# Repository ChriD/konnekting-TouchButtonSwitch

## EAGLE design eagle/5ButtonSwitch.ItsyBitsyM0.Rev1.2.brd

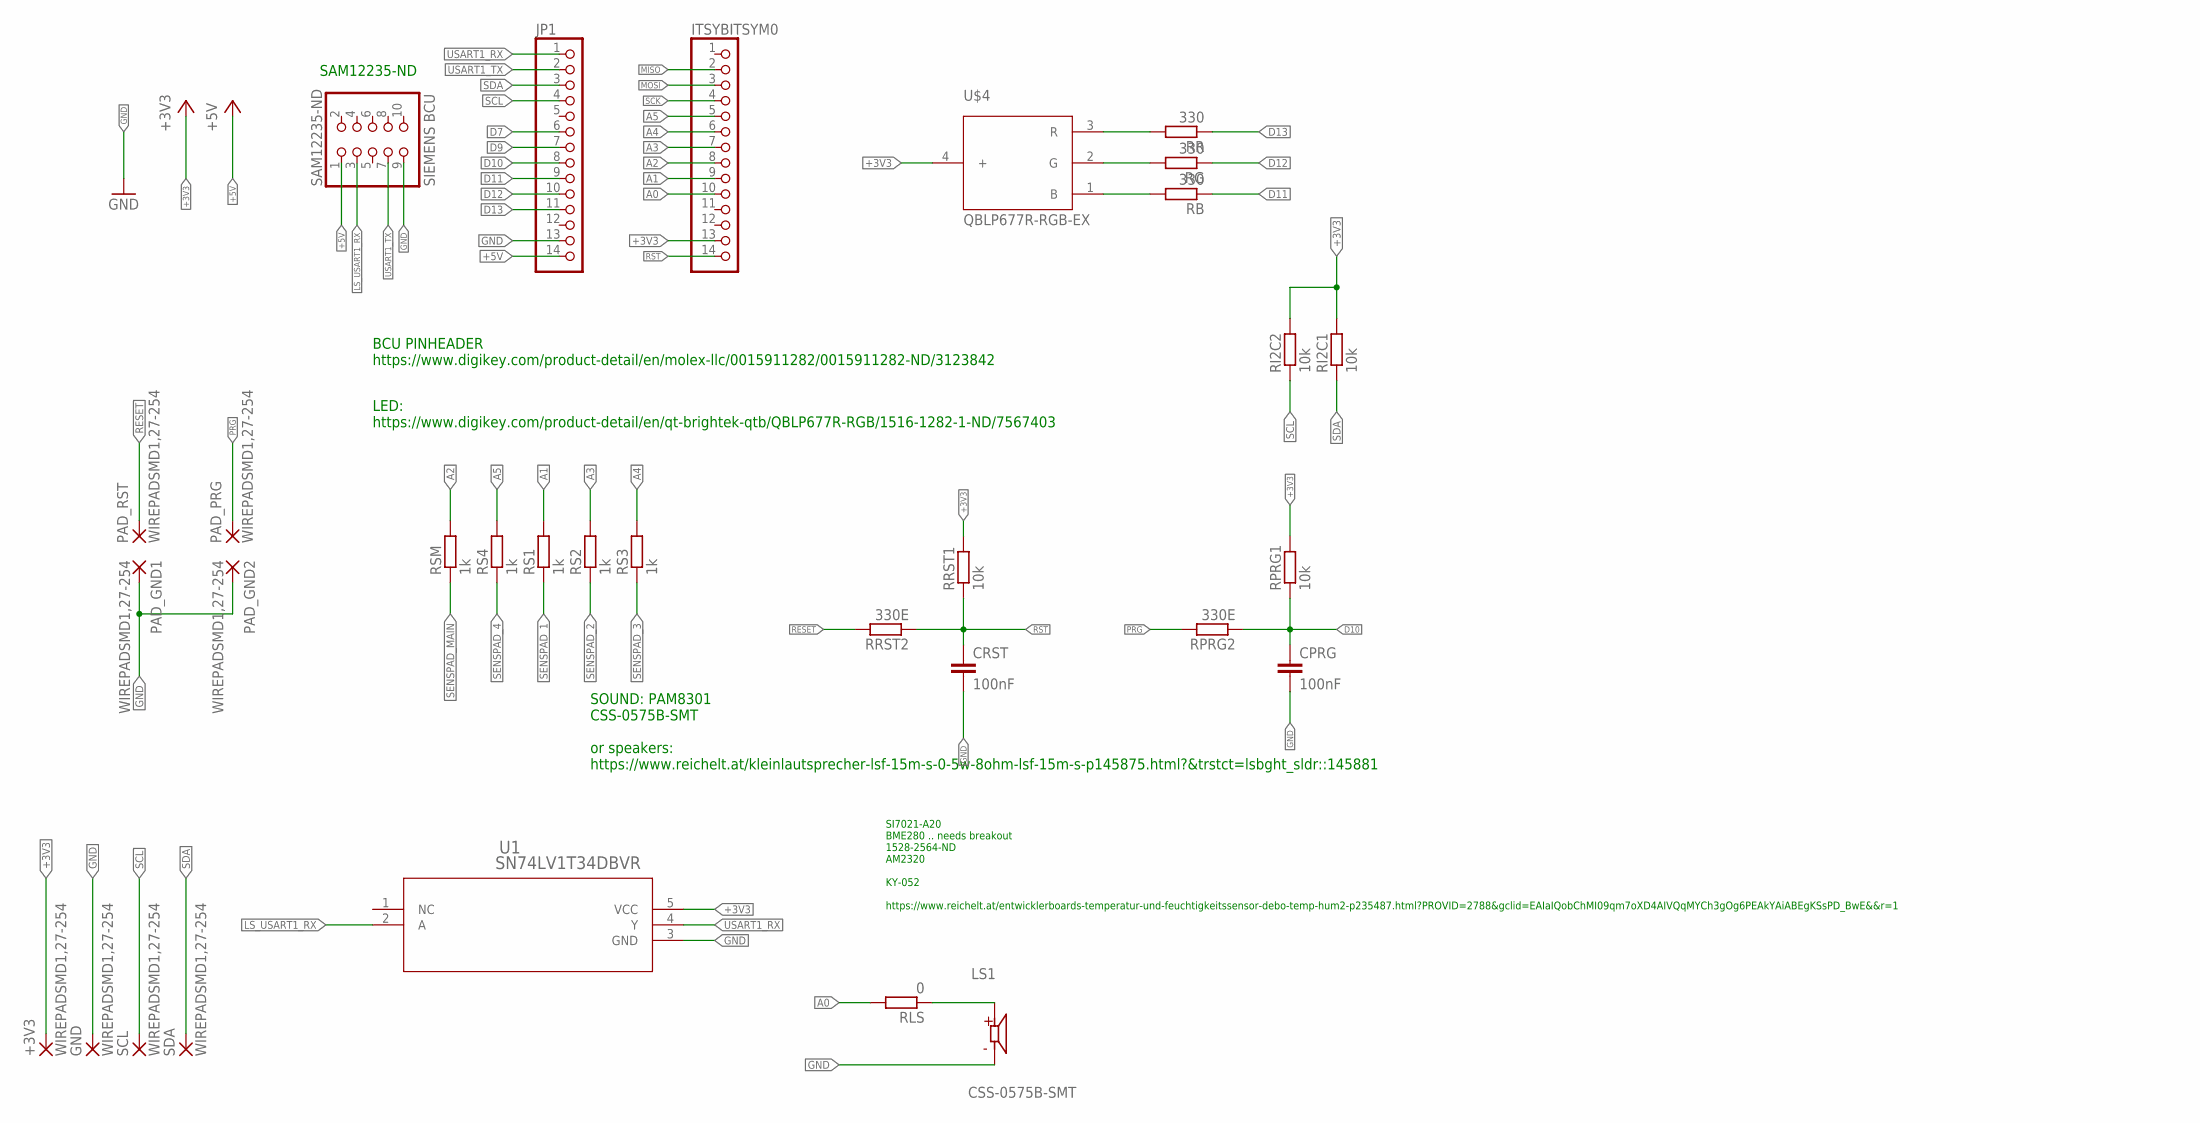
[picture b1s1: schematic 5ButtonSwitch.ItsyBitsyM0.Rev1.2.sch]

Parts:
+3V3: WIREPADSMD1,27-254; SMD1,27-2,54
CPRG: 100nF; C1206
CRST: 100nF; C1206
GND: WIREPADSMD1,27-254; SMD1,27-2,54
ITSYBITSYM0: PINHD-1X141X14_SMT; 1X14_SMT
JP1: PINHD-1X141X14_SMT; 1X14_SMT
LS1: CSS-0575B-SMT; CUI_CSS-0575B-SMT
PAD_GND1, PAD_GND2: WIREPADSMD1,27-254; SMD1,27-2,54
PAD_PRG: WIREPADSMD1,27-254; SMD1,27-2,54
PAD_RST: WIREPADSMD1,27-254; SMD1,27-2,54
RB: 330; R1206
RG: 330; R1206
RI2C1, RI2C2: 10k; R1206
RLS: 0; R1206
RPRG1: 10k; R1206
RPRG2: 330E; R1206
RR: 330; R1206
RRST1: 10k; R1206
RRST2: 330E; R1206
RS1, RS2, RS3, RS4: 1k; R1206
RSM: 1k; R1206
SAM12235-ND: SIEMENS BCU; 2X05SMD
SCL: WIREPADSMD1,27-254; SMD1,27-2,54
SDA: WIREPADSMD1,27-254; SMD1,27-2,54
U1: SN74LV1T34DBVR; DBV5
U$4: QBLP677R-RGB-EX; PLCC4R_EX

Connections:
+3V3: +3V3.1, ITSYBITSYM0.13, RI2C1.2, RI2C2.2, RPRG1.2, RRST1.2, U1.5 (VCC), U$4.4 (+)
+5V: JP1.14, SAM12235-ND.1
A0: ITSYBITSYM0.10, RLS.2
A1: ITSYBITSYM0.9, RS1.2
A2: ITSYBITSYM0.8, RSM.2
A3: ITSYBITSYM0.7, RS2.2
A4: ITSYBITSYM0.6, RS3.2
A5: ITSYBITSYM0.5, RS4.2
D7: JP1.6
D9: JP1.7
D10: CPRG.1, JP1.8, RPRG1.1, RPRG2.1
D11: JP1.9, RB.1
D12: JP1.10, RG.1
D13: JP1.11, RR.1
GND: CPRG.2, CRST.2, GND.1, JP1.13, LS1.2 (N), PAD_GND1.1, PAD_GND2.1, SAM12235-ND.9, U1.3 (GND)
LS_USART1_RX: SAM12235-ND.3, U1.2 (A)
MISO: ITSYBITSYM0.2
MOSI: ITSYBITSYM0.3
unnamed: RB.2, U$4.1 (B)
unnamed: RG.2, U$4.2 (G)
unnamed: RR.2, U$4.3 (R)
unnamed: LS1.1, RLS.1
PRG: PAD_PRG.1, RPRG2.2
RESET: PAD_RST.1, RRST2.2
RST: CRST.1, ITSYBITSYM0.14, RRST1.1, RRST2.1
SCK: ITSYBITSYM0.4
SCL: JP1.4, RI2C2.1, SCL.1
SDA: JP1.3, RI2C1.1, SDA.1
SENSPAD_1: RS1.1
SENSPAD_2: RS2.1
SENSPAD_3: RS3.1
SENSPAD_4: RS4.1
SENSPAD_MAIN: RSM.1
USART1_RX: JP1.1, U1.4 (Y)
USART1_TX: JP1.2, SAM12235-ND.7

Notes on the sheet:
SAM12235-ND
BCU PINHEADER https://www.digikey.com/product-detail/en/molex-llc/0015911282/0015911282-ND/3123842
LED: https://www.digikey.com/product-detail/en/qt-brightek-qtb/QBLP677R-RGB/1516-1282-1-ND/7567403
SI7021-A20 BME280 .. needs breakout 1528-2564-ND AM2320 KY-052 https://www.reichelt.at/entwicklerboards-temperatur-und-feuchtigkeitssensor-debo-temp-hum2-p235487.html?PROVID=2788&gclid=EAIaIQobChMI09qm7oXD4AIVQqMYCh3gOg6PEAkYAiABEgKSsPD_BwE&&r=1
SOUND: PAM8301 CSS-0575B-SMT or speakers: https://www.reichelt.at/kleinlautsprecher-lsf-15m-s-0-5w-8ohm-lsf-15m-s-p145875.html?&trstct=lsbght_sldr::145881

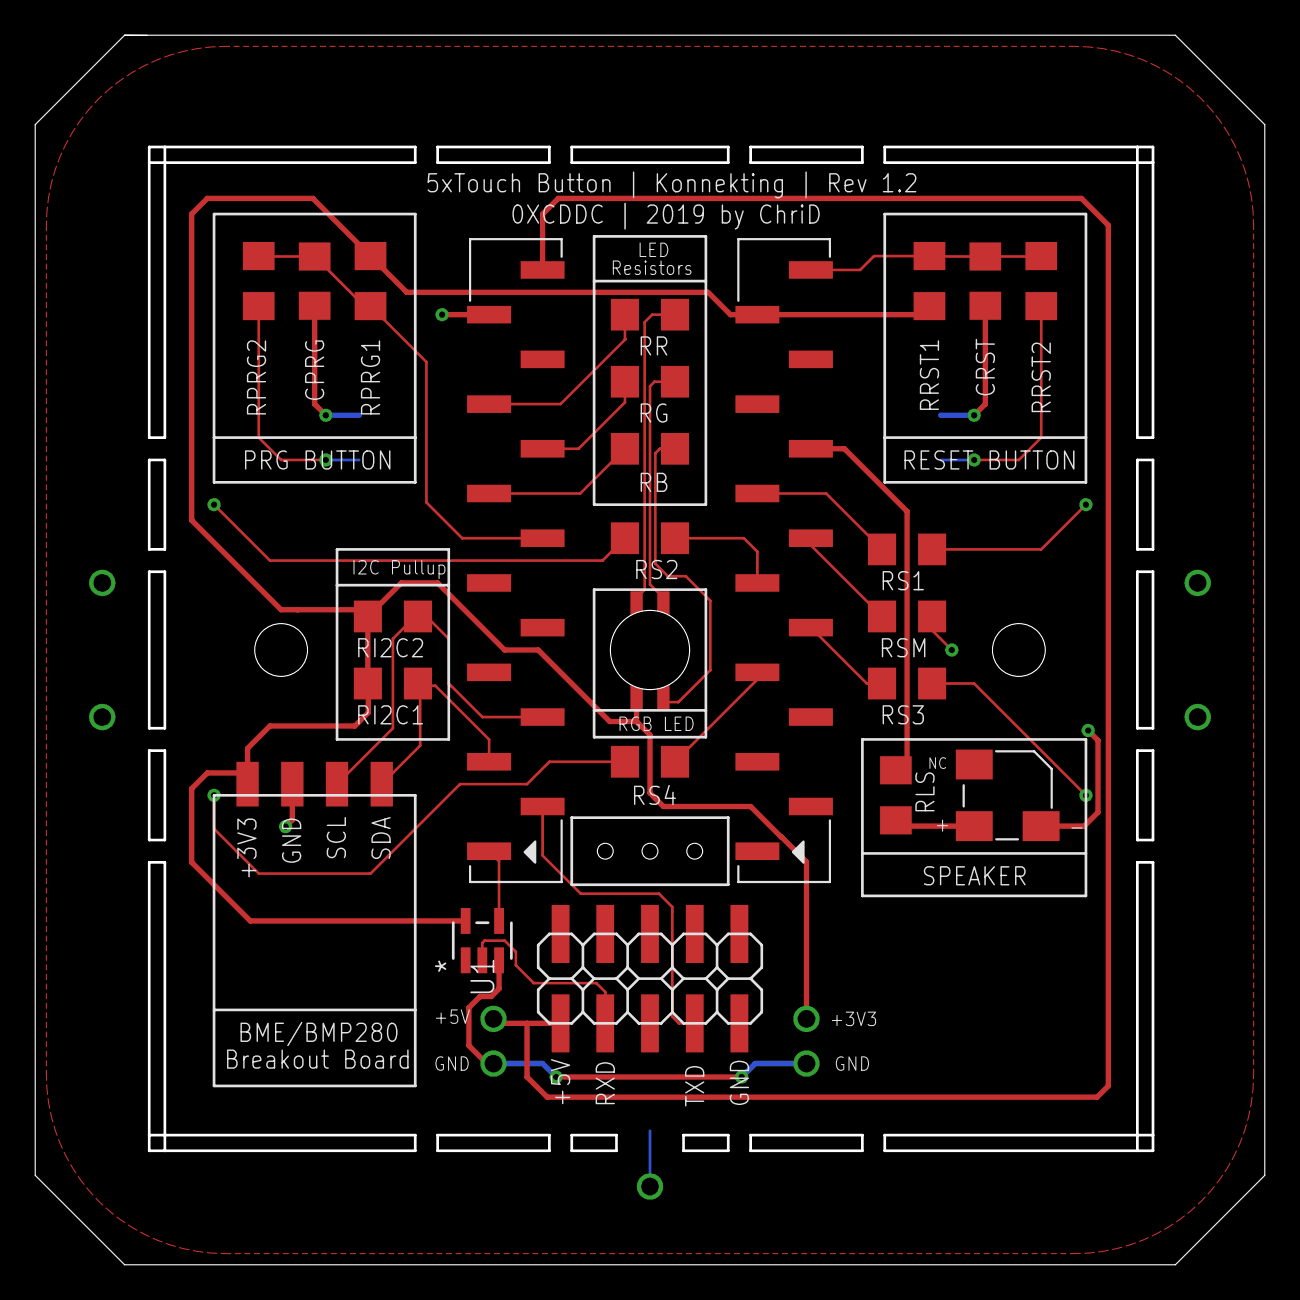
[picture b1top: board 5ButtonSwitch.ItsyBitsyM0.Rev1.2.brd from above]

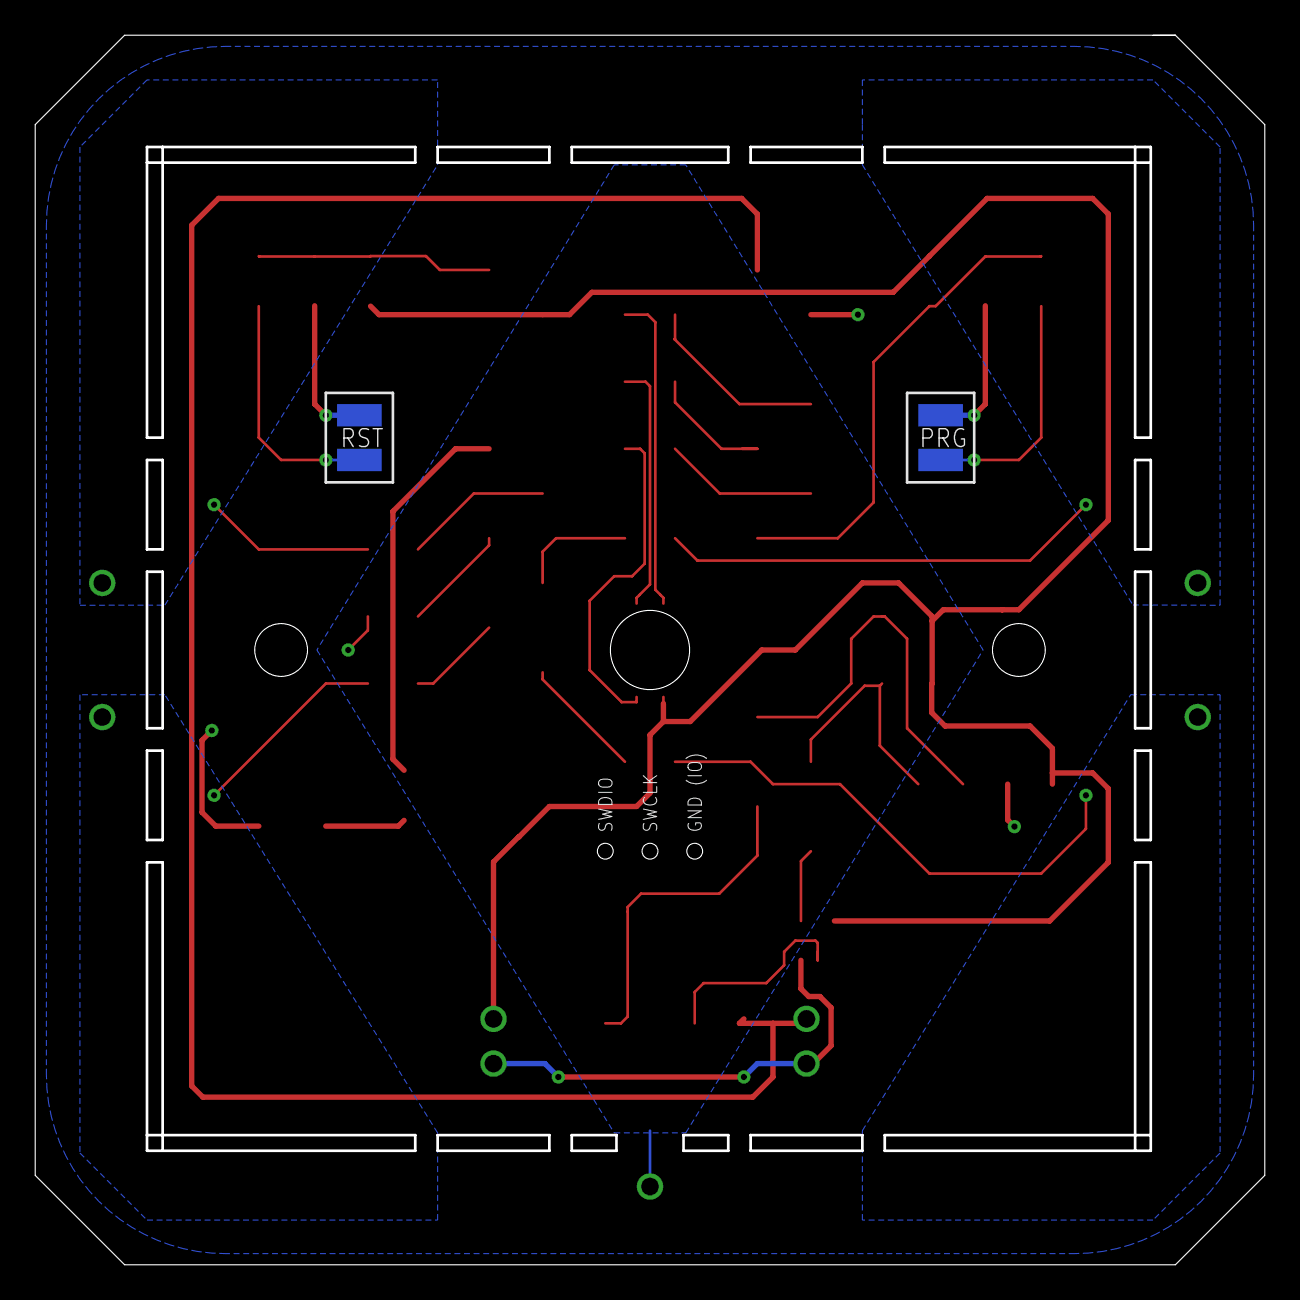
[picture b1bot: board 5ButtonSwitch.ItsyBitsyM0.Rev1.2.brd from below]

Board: 2 copper layers, 69.7 x 69.7 mm, 31 parts (4 on the bottom side), 25 nets.

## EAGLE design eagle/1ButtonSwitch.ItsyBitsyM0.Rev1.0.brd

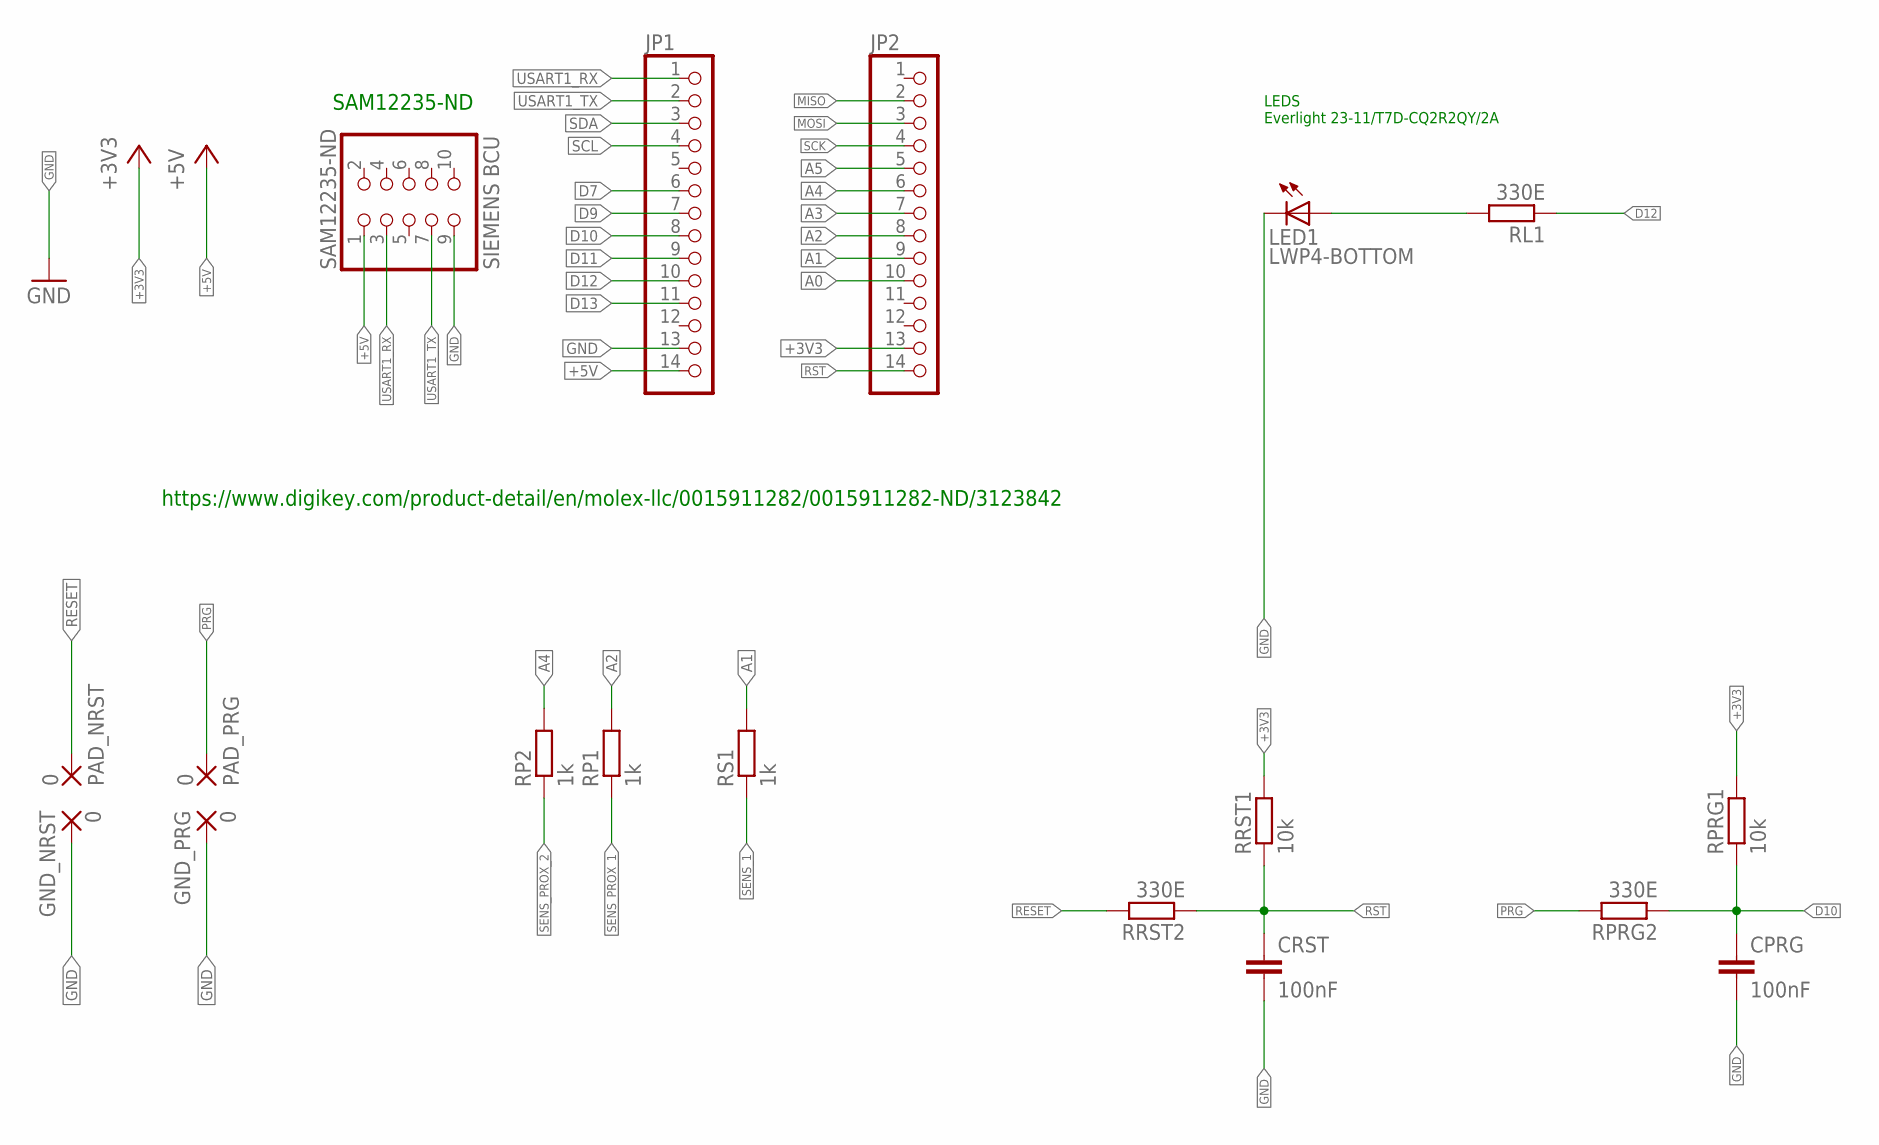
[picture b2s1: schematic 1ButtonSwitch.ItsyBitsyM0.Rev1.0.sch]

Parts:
CPRG: 100nF; C1206
CRST: 100nF; C1206
GND_NRST: 0; SMD2,54-5,08
GND_PRG: 0; SMD2,54-5,08
JP1, JP2: PINHD-1X141X14_SMT; 1X14_SMT
LED1: LWP4-BOTTOM; P47F-BOTTOM
PAD_NRST: 0; SMD2,54-5,08
PAD_PRG: 0; SMD2,54-5,08
RL1: 330E; R1206
RP1, RP2: 1k; R1206
RPRG1: 10k; R1206
RPRG2: 330E; R1206
RRST1: 10k; R1206
RRST2: 330E; R1206
RS1: 1k; R1206
SAM12235-ND: SIEMENS BCU; 2X05SMD

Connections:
+3V3: JP2.13, RPRG1.2, RRST1.2
+5V: JP1.14, SAM12235-ND.1
A0: JP2.10
A1: JP2.9, RS1.2
A2: JP2.8, RP1.2
A3: JP2.7
A4: JP2.6, RP2.2
A5: JP2.5
D7: JP1.6
D9: JP1.7
D10: CPRG.1, JP1.8, RPRG1.1, RPRG2.1
D11: JP1.9
D12: JP1.10, RL1.1
D13: JP1.11
GND: CPRG.2, CRST.2, GND_NRST.1, GND_PRG.1, JP1.13, LED1.C, SAM12235-ND.9
MISO: JP2.2
MOSI: JP2.3
unnamed: LED1.A, RL1.2
PRG: PAD_PRG.1, RPRG2.2
RESET: PAD_NRST.1, RRST2.2
RST: CRST.1, JP2.14, RRST1.1, RRST2.1
SCK: JP2.4
SCL: JP1.4
SDA: JP1.3
SENS_1: RS1.1
SENS_PROX_1: RP1.1
SENS_PROX_2: RP2.1
USART1_RX: JP1.1, SAM12235-ND.3
USART1_TX: JP1.2, SAM12235-ND.7

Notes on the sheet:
SAM12235-ND
LEDS Everlight 23-11/T7D-CQ2R2QY/2A
https://www.digikey.com/product-detail/en/molex-llc/0015911282/0015911282-ND/3123842

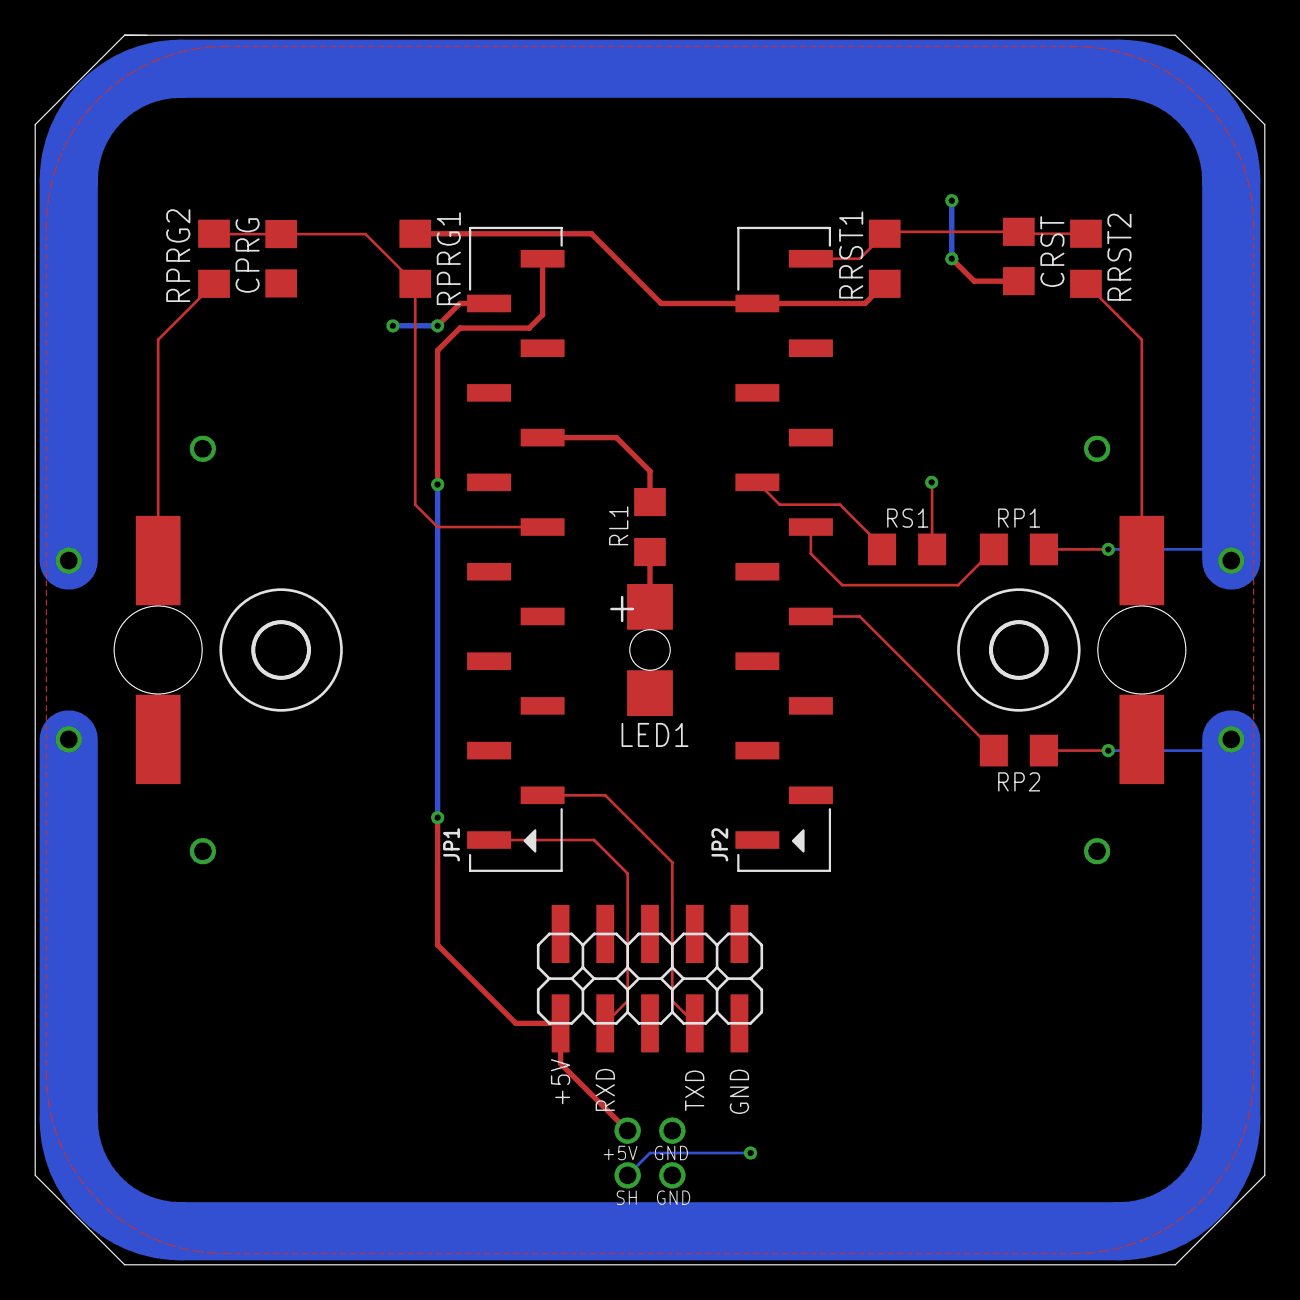
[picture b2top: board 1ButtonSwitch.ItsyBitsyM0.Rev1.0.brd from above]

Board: 2 copper layers, 69.8 x 69.8 mm, 20 parts (0 on the bottom side), 14 nets.

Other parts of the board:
U$1, U$2: 3,0

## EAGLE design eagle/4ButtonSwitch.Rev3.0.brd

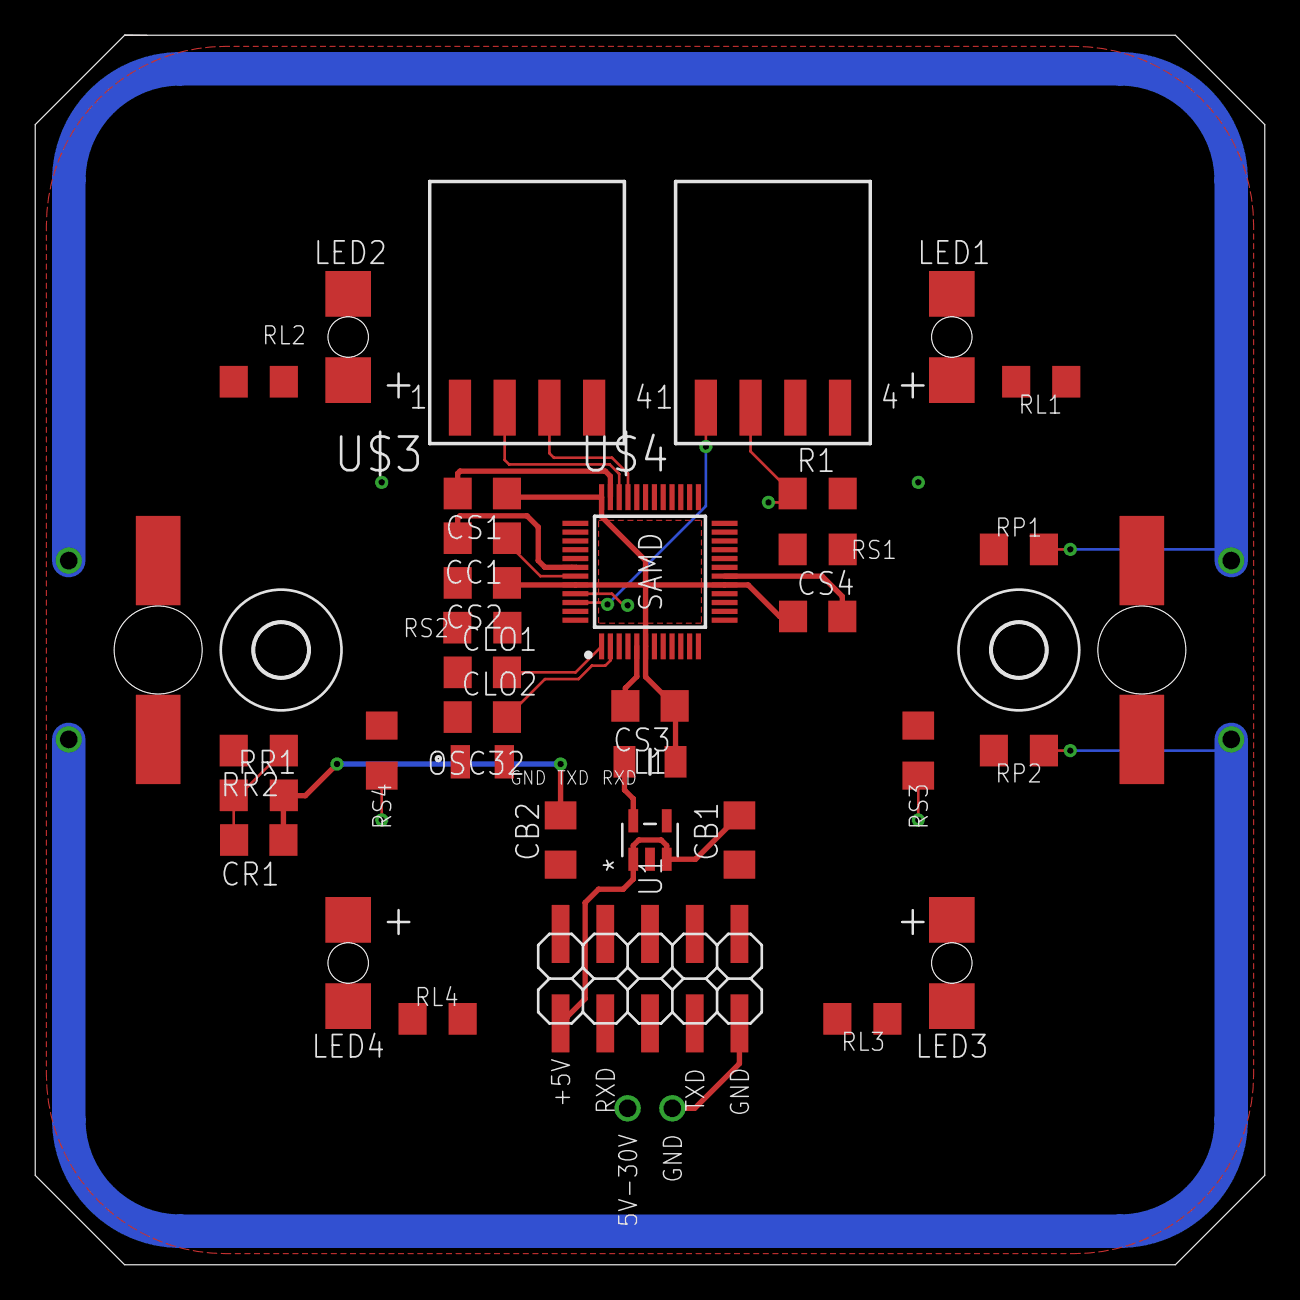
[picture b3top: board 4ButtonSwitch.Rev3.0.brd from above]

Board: 2 copper layers, 69.8 x 69.8 mm, 40 parts (0 on the bottom side), 23 nets.

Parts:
CB1: 4.7uF; C1206
CB2: 10uF; C1206
CC1: 1uF; C1206
CLO1, CLO2: 15pF; C1206
CR1: 100pF; C1206
CS1, CS2, CS3, CS4: 100nf; C1206
GND_NRST: 0; SMD2,54-5,08
GND_PRG: 0; SMD2,54-5,08
L1: LQM31PN1R0M00L; INDC3216X95N
LED1, LED2, LED3, LED4: LWP4-BOTTOM; P47F-BOTTOM
OSC32: ABS07-32.768KHZ-7-T; ABS-07
PAD_NRST: 0; SMD2,54-5,08
PAD_PRG: 0; SMD2,54-5,08
R1: 1k; R1206
RL1, RL2, RL3, RL4: 330E; R1206
RP1, RP2: 1k; R1206
RR1: 2.2k; R1206
RR2: 330E; R1206
RS1, RS2, RS3, RS4: 1k; R1206
SAM12235-ND: SIEMENS BCU; 2X05SMD
SAMD: ATSAMD21G18A-AU; QFP50P900X900X120-48N
U1: ADP2108AUJZ-3.3-R7; UJ_5
U$1, U$2: 3,0
U$3, U$4: SAMTEC-TSM-104-01-X-SHJ; SAMTEC-TSM-104-01-X-SH

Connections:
+3V3: CB2.2, CR1.1, CS1.1, CS2.1, CS3.1, CS4.1, L1.2, R1.2, RR1.2, SAMD.6, SAMD.17, SAMD.36, SAMD.44, U1.4
+5V: CB1.2, SAM12235-ND.1, U1.1, U1.3
GND: CB1.1, CB2.1, CC1.2, CLO1.1, CLO2.1, CS1.2, CS2.2, CS3.2, CS4.2, GND_NRST.1, GND_PRG.1, LED1.C, LED2.C, LED3.C, LED4.C, SAM12235-ND.9, SAMD.5, SAMD.18, SAMD.35, SAMD.42, U1.2, U$3.1, U$4.4
unnamed: L1.1, U1.5
unnamed: LED1.A, RL1.2
unnamed: LED2.A, RL2.2
unnamed: LED3.A, RL3.2
unnamed: LED4.A, RL4.2
NRST: CR1.2, RR1.1, RR2.1, SAMD.40
PA02: RS4.2, SAMD.3
PA04: RP2.2, SAMD.9
PA05: RP1.2, SAMD.10
PA07: RS1.2, SAMD.12
PB02: RS2.2, SAMD.47
PB08: RS3.2, SAMD.7
RESET: PAD_NRST.1, RR2.2, U$4.3
SWCLK: R1.1, SAMD.45, U$4.2
SWDIO: SAMD.46, U$4.1
USB+: SAMD.34, U$3.2
USB-: SAMD.33, U$3.3
VDDCORE: CC1.1, SAMD.43
X32IN: CLO1.2, OSC32.1, SAMD.1
X32OUT: CLO2.2, OSC32.2, SAMD.2

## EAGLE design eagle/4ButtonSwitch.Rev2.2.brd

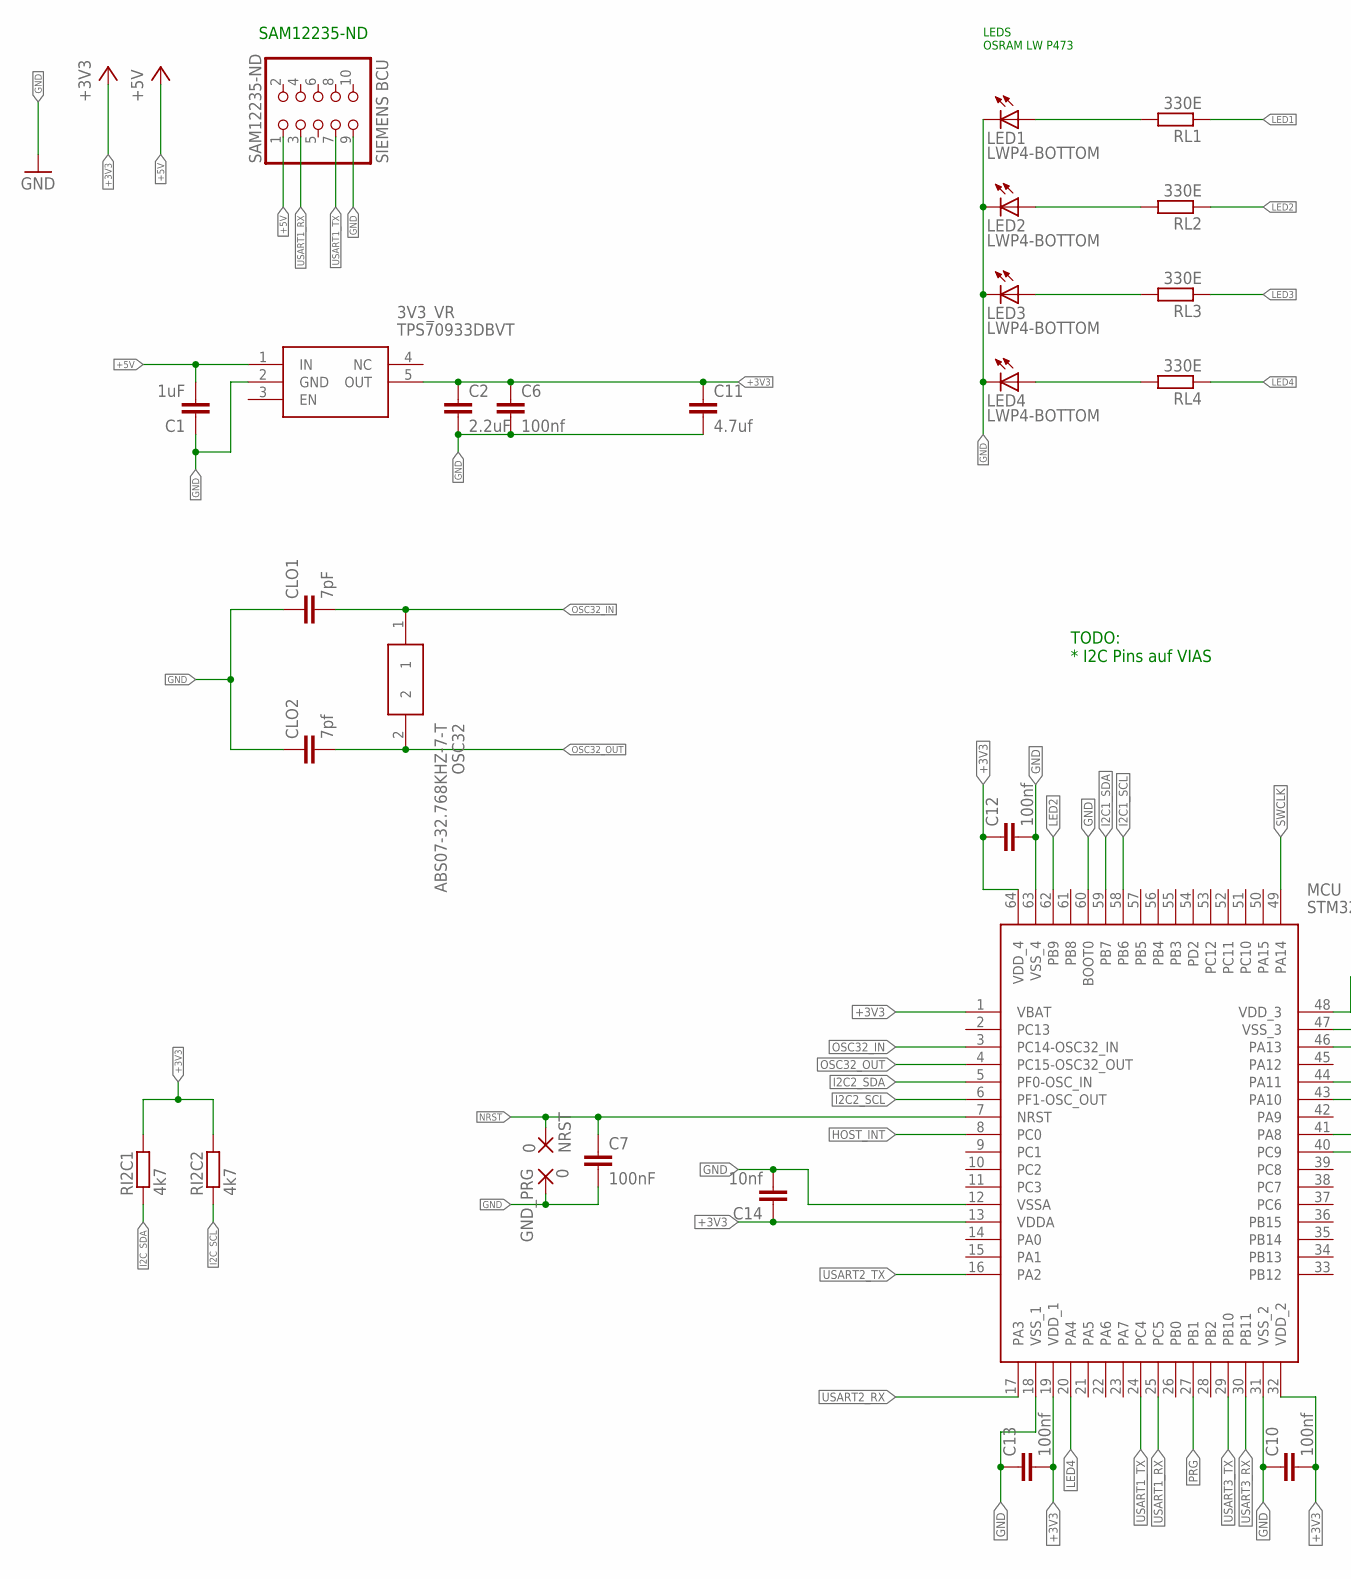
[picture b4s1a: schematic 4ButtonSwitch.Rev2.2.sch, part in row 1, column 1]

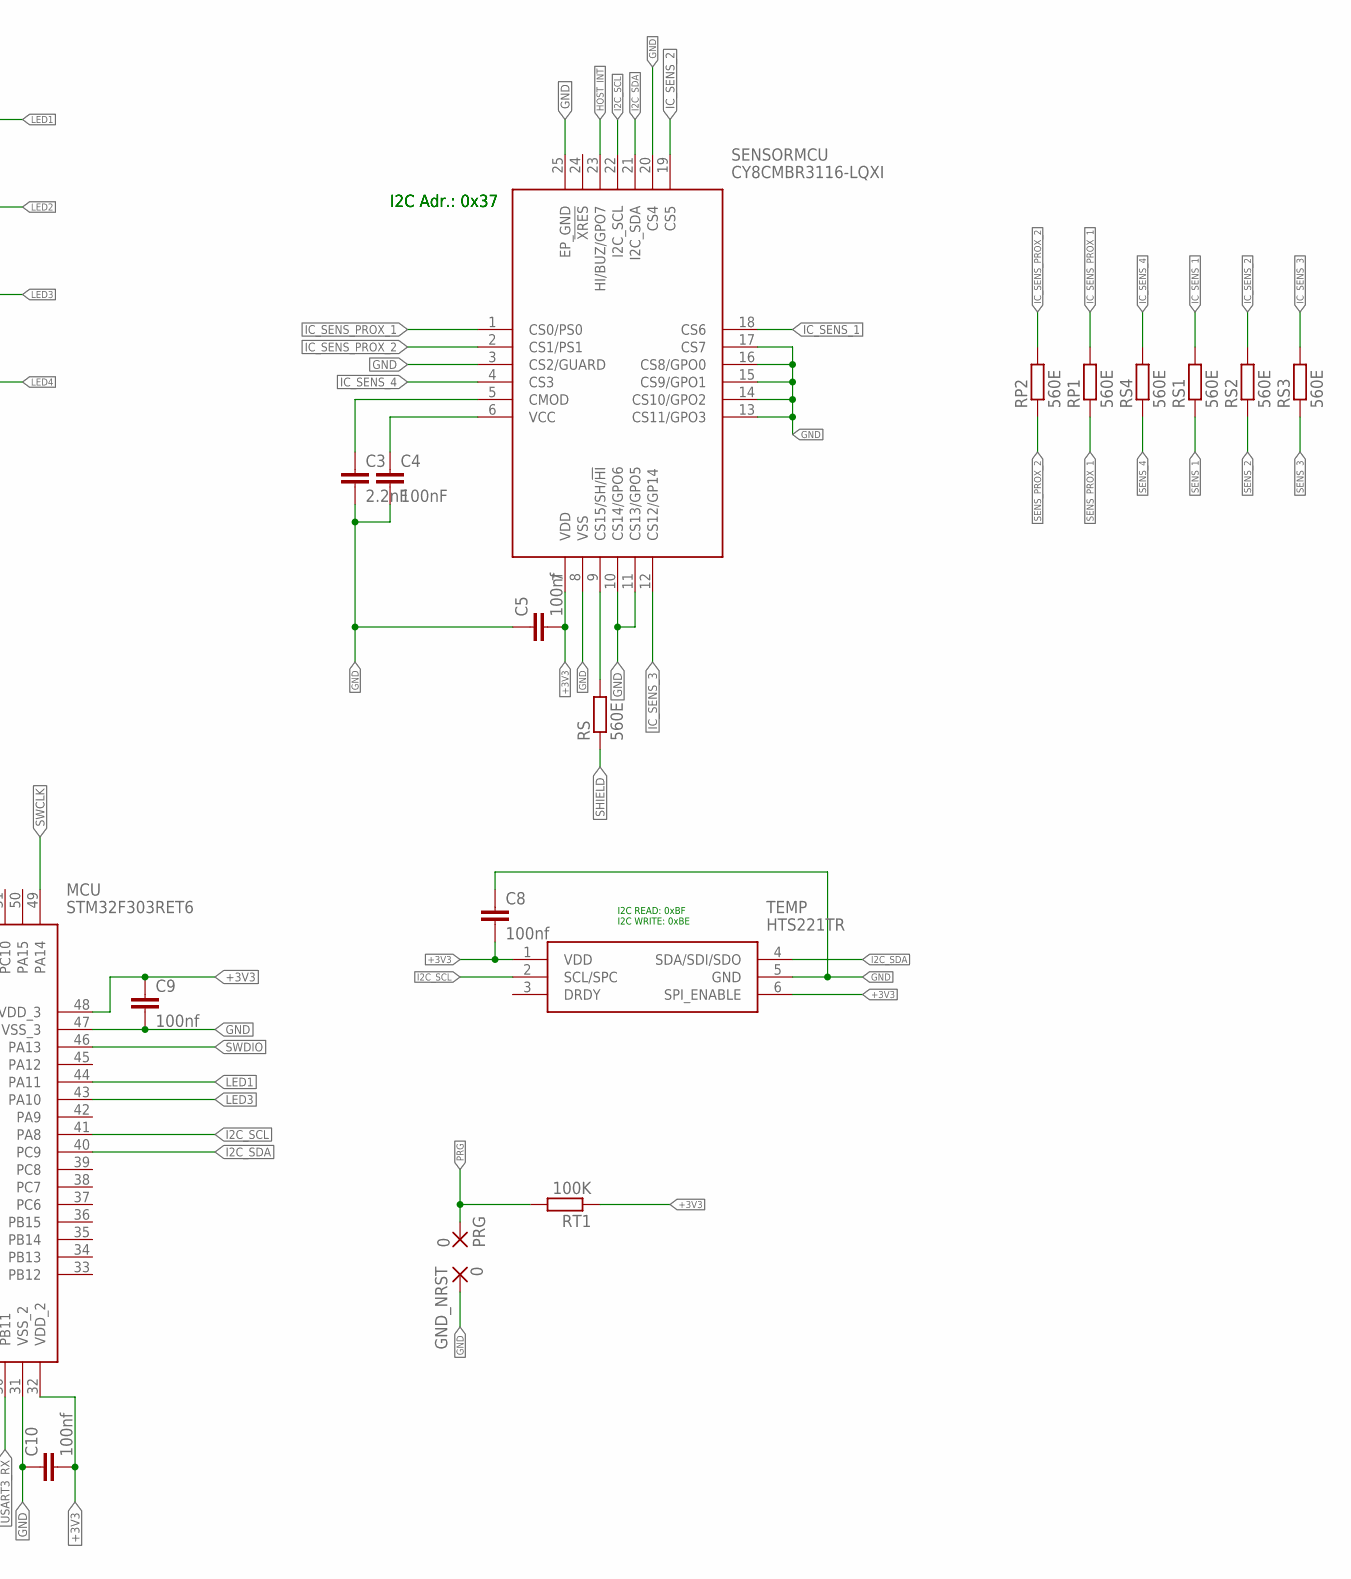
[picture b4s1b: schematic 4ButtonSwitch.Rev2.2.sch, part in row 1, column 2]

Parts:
3V3_VR: TPS70933DBVT; SOT95P280X145-5N
C1: 1uF; C0402
C2: 2.2uF; C0402
C3: 2.2nF; C0402
C4, C7: 100nF; C0402
C5, C6, C8, C9, C10, C12, C13: 100nf; C0402
C11: 4.7uf; C0402
C14: 10nf; C0402
CLO1: 7pF; C0402
CLO2: 7pf; C0402
GND_NRST: 0; SMD2,54-5,08
GND_PRG: 0; SMD2,54-5,08
LED1, LED2, LED3, LED4: LWP4-BOTTOM; P47F-BOTTOM
MCU: STM32F303RET6; QFP50P1200X1200X160-64N
NRST: 0; SMD2,54-5,08
OSC32: ABS07-32.768KHZ-7-T; ABS-07
PRG: 0; SMD2,54-5,08
RI2C1, RI2C2: 4k7; R0402
RL1, RL2, RL3, RL4: 330E; R0402
RP1, RP2: 560E; R0402
RS, RS1, RS2, RS3, RS4: 560E; R0402
RT1: 100K; R0402
SAM12235-ND: SIEMENS BCU; 2X05SMD
SENSORMCU: CY8CMBR3116-LQXI; QFN50P400X400X60-25N
TEMP: HTS221TR; HLGA-6L

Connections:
+3V3: 3V3_VR.5 (OUT), C2.1, C5.2, C6.1, C8.2, C9.1, C10.2, C11.1, C12.1, C13.2, C14.1, MCU.1 (VBAT), MCU.13 (VDDA), MCU.19 (VDD_1), MCU.32 (VDD_2), MCU.48 (VDD_3), MCU.64 (VDD_4), RI2C1.2, RI2C2.2, RT1.1, SENSORMCU.7 (VDD), TEMP.1 (VDD), TEMP.6 (SPI_ENABLE)
+5V: 3V3_VR.1 (IN), C1.2, SAM12235-ND.1
CMOD: C3.1, SENSORMCU.5 (CMOD)
GND: 3V3_VR.2 (GND), C1.1, C2.2, C3.2, C4.2, C5.1, C6.2, C7.2, C8.1, C9.2, C10.1, C11.2, C12.2, C13.1, C14.2, CLO1.1, CLO2.1, GND_NRST.1, GND_PRG.1, LED1.C, LED2.C, LED3.C, LED4.C, MCU.12 (VSSA), MCU.18 (VSS_1), MCU.31 (VSS_2), MCU.47 (VSS_3), MCU.60 (BOOT0), MCU.63 (VSS_4), SAM12235-ND.9, SENSORMCU.3 (CS2/GUARD), SENSORMCU.8 (VSS), SENSORMCU.10 (CS14/GPO6), SENSORMCU.11 (CS13/GPO5), SENSORMCU.13 (CS11/GPO3), SENSORMCU.14 (CS10/GPO2), SENSORMCU.15 (CS9/GPO1), SENSORMCU.16 (CS8/GPO0), SENSORMCU.17 (CS7), SENSORMCU.20 (CS4), SENSORMCU.25 (EP_GND), TEMP.5 (GND)
HOST_INT: MCU.8 (PC0), SENSORMCU.23 (HI/BUZ/GPO7)
I2C1_SCL: MCU.58 (PB6)
I2C1_SDA: MCU.59 (PB7)
I2C2_SCL: MCU.6 (PF1-OSC_OUT)
I2C2_SDA: MCU.5 (PF0-OSC_IN)
I2C_SCL: MCU.41 (PA8), RI2C2.1, SENSORMCU.22 (I2C_SCL), TEMP.2 (SCL/SPC)
I2C_SDA: MCU.40 (PC9), RI2C1.1, SENSORMCU.21 (I2C_SDA), TEMP.4 (SDA/SDI/SDO)
IC_SENS_1: RS1.2, SENSORMCU.18 (CS6)
IC_SENS_2: RS2.2, SENSORMCU.19 (CS5)
IC_SENS_3: RS3.2, SENSORMCU.12 (CS12/GP14)
IC_SENS_4: RS4.2, SENSORMCU.4 (CS3)
IC_SENS_PROX_1: RP1.2, SENSORMCU.1 (CS0/PS0)
IC_SENS_PROX_2: RP2.2, SENSORMCU.2 (CS1/PS1)
LED1: MCU.44 (PA11), RL1.1
LED2: MCU.62 (PB9), RL2.1
LED3: MCU.43 (PA10), RL3.1
LED4: MCU.20 (PA4), RL4.1
unnamed: RS.2, SENSORMCU.9 (CS15/SH/!HI)
unnamed: LED1.A, RL1.2
unnamed: LED2.A, RL2.2
unnamed: LED3.A, RL3.2
unnamed: LED4.A, RL4.2
NRST: C7.1, MCU.7 (NRST), NRST.1
OSC32_IN: CLO1.2, MCU.3 (PC14-OSC32_IN), OSC32.1
OSC32_OUT: CLO2.2, MCU.4 (PC15-OSC32_OUT), OSC32.2
PRG: MCU.27 (PB1), PRG.1, RT1.2
SENS_1: RS1.1
SENS_2: RS2.1
SENS_3: RS3.1
SENS_4: RS4.1
SENS_PROX_1: RP1.1
SENS_PROX_2: RP2.1
SHIELD: RS.1
SWCLK: MCU.49 (PA14)
SWDIO: MCU.46 (PA13)
USART1_RX: MCU.25 (PC5), SAM12235-ND.3
USART1_TX: MCU.24 (PC4), SAM12235-ND.7
USART2_RX: MCU.17 (PA3)
USART2_TX: MCU.16 (PA2)
USART3_RX: MCU.30 (PB11)
USART3_TX: MCU.29 (PB10)
VCC: C4.1, SENSORMCU.6 (VCC)

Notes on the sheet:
I2C READ: 0xBF I2C WRITE: 0xBE
I2C Adr.: 0x37
SAM12235-ND
TODO: * I2C Pins auf VIAS
LEDS OSRAM LW P473

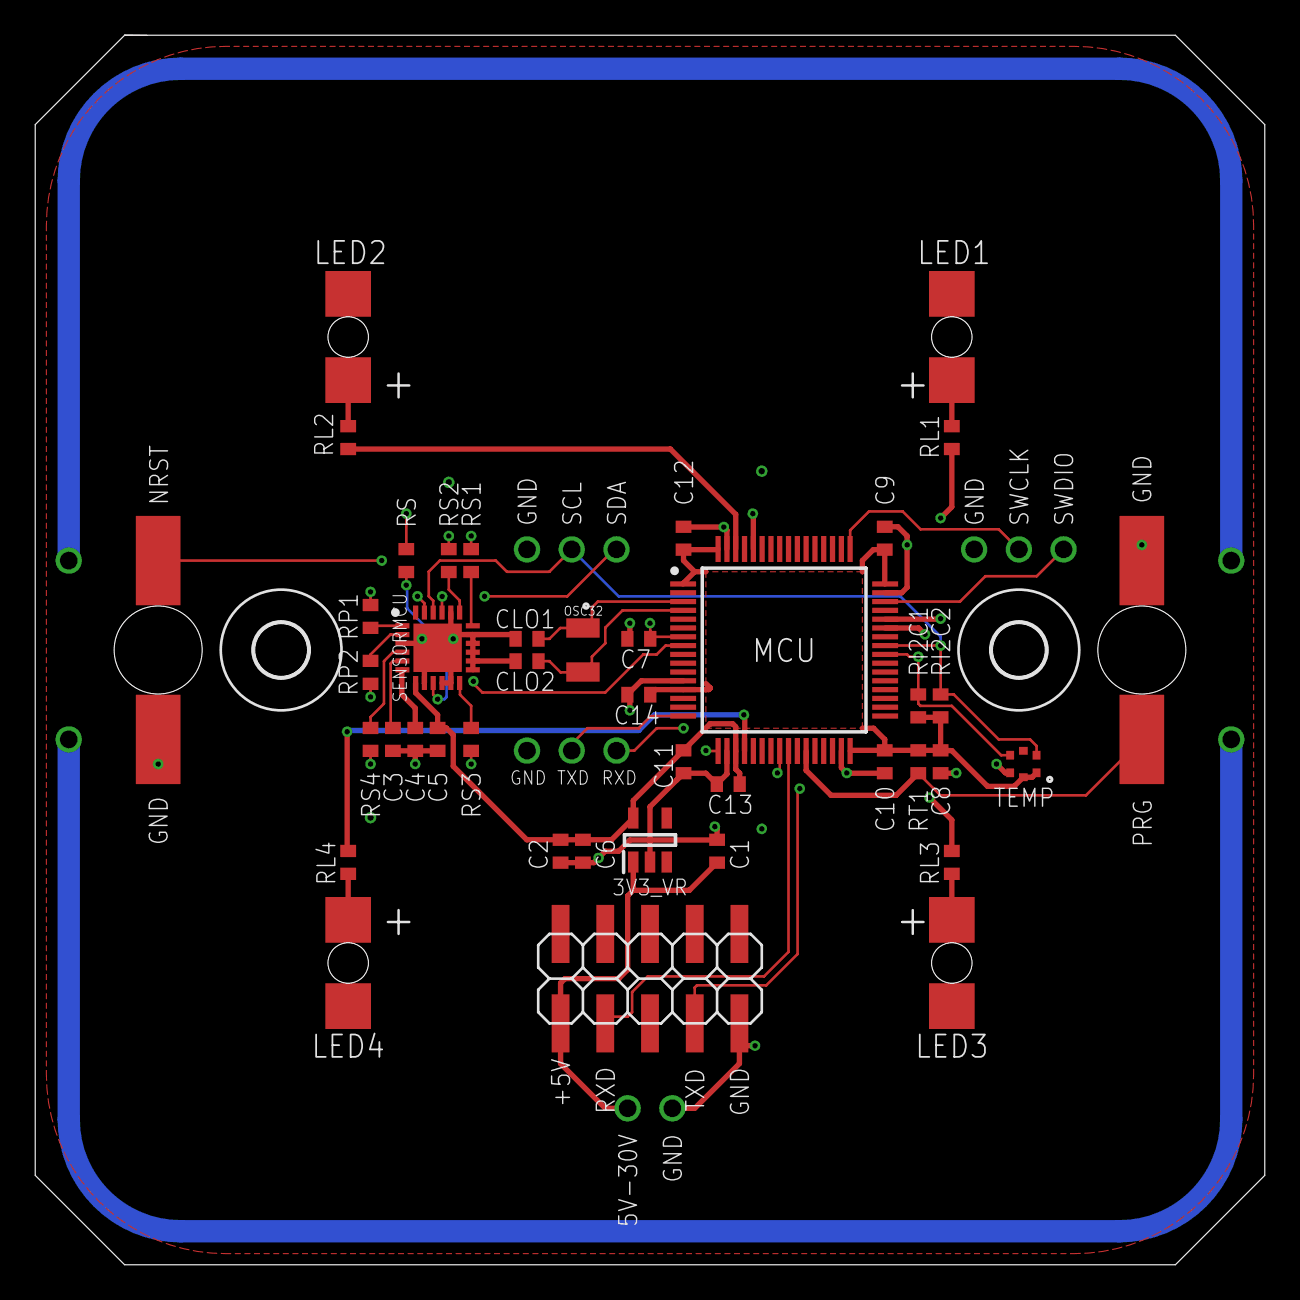
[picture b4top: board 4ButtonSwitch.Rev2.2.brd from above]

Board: 4 copper layers, 69.8 x 69.8 mm, 46 parts (0 on the bottom side), 29 nets.

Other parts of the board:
U$1, U$2: 3,0

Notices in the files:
parts and their libraries:
Wurth_Elektronik_Optoelectronics_rev15b: Copyright: Würth Elektronik
tag-connect: ©2009 ROFA.cz - modified and updated by Robert Darlington ‹rdarlington@gmail.com›
